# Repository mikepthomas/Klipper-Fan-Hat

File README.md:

# Klipper Fan Hat

[Interactive bom](https://mikethomas.info/Klipper-Fan-Hat)

### A Hat to use with the [Raspberry Pi as a Secondary MCU in Klipper](https://www.klipper3d.org/RPi_microcontroller.html):
- SKR Pico compatible input for powering the Pi and Serial communication
- 5 Mosfet outputs (with 2 pin JST-XH connectors standard on most fans used on 3D printers)
- Voltage selector jumpers to power each fan from either 5V or VCC supplied by screw terminal
- I2C and 1-Wire and SPI headers for connecting accesories to the Raspberry Pi
- 2 headers connected to General Purpose GPIO pins for accesories such as Filament Run Out Sensors

### Documentation

[Documentation and Setup information here](Documentation/README.md)

 Parts that I sourced for assembly:
- 1206 Capacitor Set [Ali Express](https://www.aliexpress.com/item/1005002907508304.html)
- 1206 LEDs [Ali Express](https://www.aliexpress.com/item/1005003836509392.html)
- 1206 Resistor Set [Ali Express](https://www.aliexpress.com/item/33029877427.html)
- 2510 Axial Fan [Ali Express](https://www.aliexpress.com/item/32807610078.html)
- Blade Fuse Holder [Ali Express](https://www.aliexpress.com/item/1005003194700697.html)
- DIP-8 24C32 EEPROM [Ali Express](https://www.aliexpress.com/item/33036366759.html)
- DIP-8 Socket [Ali Express](https://www.aliexpress.com/item/1005001650813894.html)
- IRLML6344TRPBF Mosfets [Ali Express](https://www.aliexpress.com/item/1005004711783484.html)
- JST-XH Connector Set [Ali Express](https://www.aliexpress.com/item/33000442968.html)
- Jumper Caps [Ali Express](https://www.aliexpress.com/item/1005004482029258.html)
- KF301 Screw Terminal [Ali Express](https://www.aliexpress.com/item/1005003311688833.html)
- M2.5x14 BHCS [Ali Express](https://www.aliexpress.com/item/1005004123548619.html)
- Pin Header Set [Amazon](https://www.amazon.co.uk/gp/product/B07CWSXY7P)
- Raspberry Pi Headers and Spacers [Amazon](https://www.amazon.co.uk/gp/product/B07PHBTTGV)

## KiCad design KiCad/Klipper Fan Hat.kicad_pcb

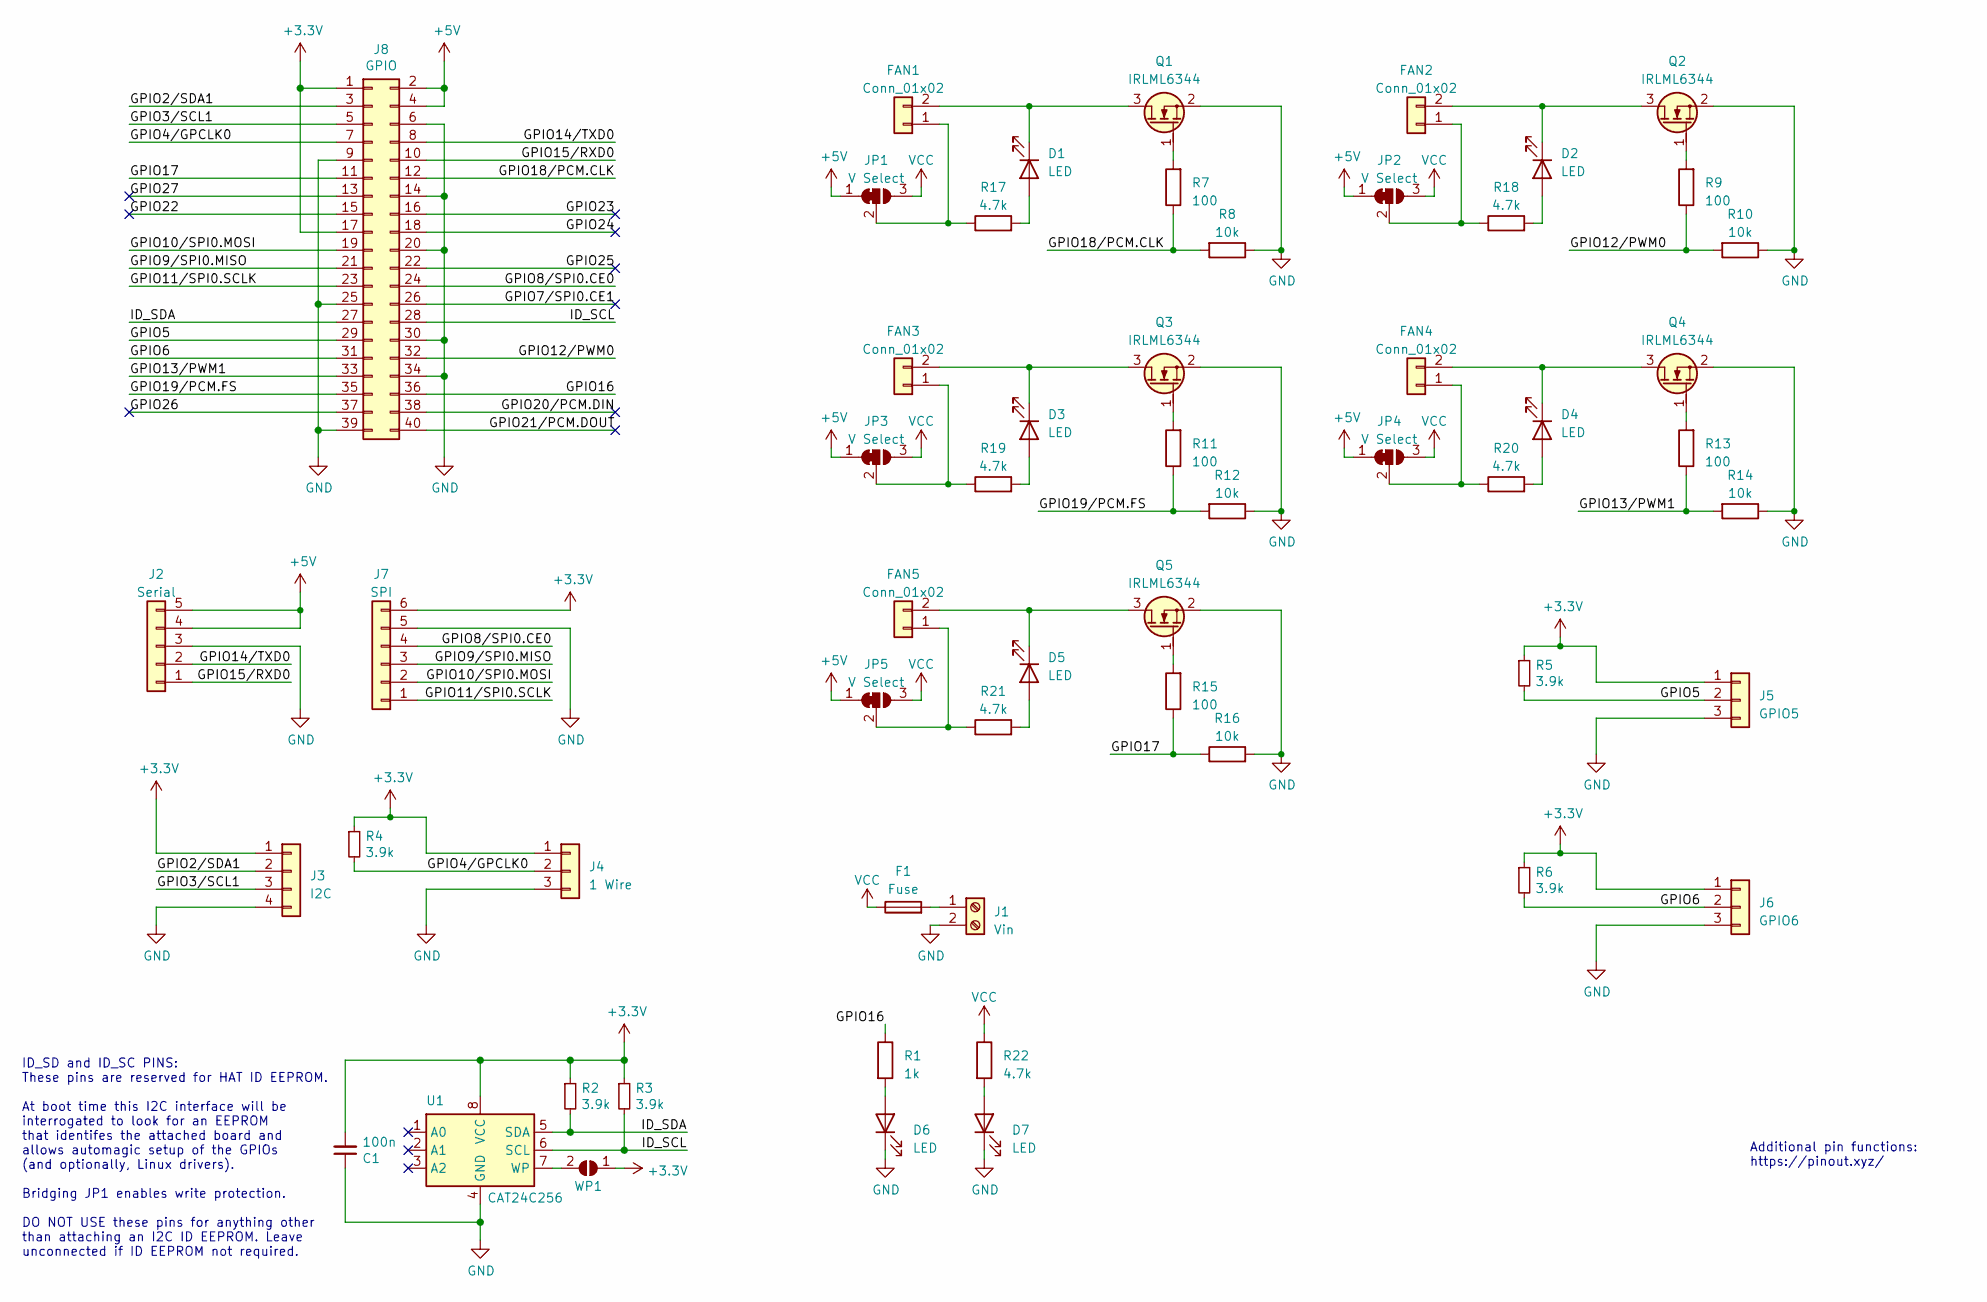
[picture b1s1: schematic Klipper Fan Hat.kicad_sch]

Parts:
C1: 100n; C_1206_3216Metric
D1, D2, D3, D4, D5, D6, D7: LED; LED_1206_3216Metric_ReverseMount_Hole1.8x2.4mm
F1: Fuse; Fuseholder_Blade_Mini_Keystone_3568
FAN1, FAN2, FAN3, FAN4, FAN5: Conn_01x02; JST_XH_B2B-XH-A_1x02_P2.50mm_Vertical
J1: Vin; TerminalBlock_bornier-2_P5.08mm
J2: Serial; JST_XH_B5B-XH-A_1x05_P2.50mm_Vertical
J3: I2C; JST_XH_B4B-XH-A_1x04_P2.50mm_Vertical
J4: 1 Wire; JST_XH_B3B-XH-A_1x03_P2.50mm_Vertical
J5: GPIO5; JST_XH_B3B-XH-A_1x03_P2.50mm_Vertical
J6: GPIO6; JST_XH_B3B-XH-A_1x03_P2.50mm_Vertical
J7: SPI; PinHeader_1x06_P2.54mm_Vertical
J8: GPIO; PinSocket_2x20_P2.54mm_Vertical
JP1, JP2, JP3, JP4, JP5: V Select; PinHeader_1x03_P2.54mm_Vertical
Q1, Q2, Q3, Q4, Q5: IRLML6344; TSOT-23
R1: 1k; R_1206_3216Metric
R2, R3, R4, R5, R6: 3.9k; R_1206_3216Metric
R7, R9, R11, R13, R15: 100; R_1206_3216Metric
R8, R10, R12, R14, R16: 10k; R_1206_3216Metric
R17, R18, R19, R20, R21, R22: 4.7k; R_1206_3216Metric
U1: CAT24C256; DIP-8_W7.62mm
WP1: ID_WP; PinHeader_1x02_P2.54mm_Vertical

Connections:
+3V3: C1.2, J3.1, J4.1, J5.1, J6.1, J7.6, J8.1, J8.17, R2.1, R3.1, R4.1, R5.1, R6.1, U1.8 (VCC), WP1.1 (A)
+5V: J2.4, J2.5, J8.2, J8.4, JP1.1 (A), JP2.1 (A), JP3.1 (A), JP4.1 (A), JP5.1 (A)
/GPIO2/SDA1: J3.2, J8.3
/GPIO3/SCL1: J3.3, J8.5
/GPIO4/GPCLK0: J4.2, J8.7, R4.2
/GPIO5: J5.2, J8.29, R5.2
/GPIO6: J6.2, J8.31, R6.2
/GPIO7/SPI0.CE1: J8.26
/GPIO8/SPI0.CE0: J7.4, J8.24
/GPIO9/SPI0.MISO: J7.3, J8.21
/GPIO10/SPI0.MOSI: J7.2, J8.19
/GPIO11/SPI0.SCLK: J7.1, J8.23
/GPIO12/PWM0: J8.32, R9.1, R10.2
/GPIO13/PWM1: J8.33, R13.1, R14.2
/GPIO14/TXD0: J2.2, J8.8
/GPIO15/RXD0: J2.1, J8.10
/GPIO16: J8.36, R1.1
/GPIO17: J8.11, R15.1, R16.1
/GPIO18/PCM.CLK: J8.12, R7.1, R8.2
/GPIO19/PCM.FS: J8.35, R11.1, R12.2
/GPIO20/PCM.DIN: J8.38
/GPIO21/PCM.DOUT: J8.40
/GPIO22: J8.15
/GPIO23: J8.16
/GPIO24: J8.18
/GPIO25: J8.22
/GPIO26: J8.37
/GPIO27: J8.13
/ID_SCL: J8.28, R3.2, U1.6 (SCL)
/ID_SDA: J8.27, R2.2, U1.5 (SDA)
GND: C1.1, D6.1 (K), D7.1 (K), J1.2, J2.3, J3.4, J4.3, J5.3, J6.3, J7.5, J8.6, J8.9, J8.14, J8.20, J8.25, J8.30, J8.34, J8.39, Q1.2 (S), Q2.2 (S), Q3.2 (S), Q4.2 (S), Q5.2 (S), R8.1, R10.1, R12.1, R14.1, R16.2, U1.4 (GND)
unnamed: D1.2 (A), R17.2
unnamed: D1.1 (K), FAN1.2, Q1.3 (D)
unnamed: D2.2 (A), R18.2
unnamed: D2.1 (K), FAN2.2, Q2.3 (D)
unnamed: D3.2 (A), R19.2
unnamed: D3.1 (K), FAN3.2, Q3.3 (D)
unnamed: D4.2 (A), R20.2
unnamed: D4.1 (K), FAN4.2, Q4.3 (D)
unnamed: D5.2 (A), R21.2
unnamed: D5.1 (K), FAN5.2, Q5.3 (D)
unnamed: D6.2 (A), R1.2
unnamed: D7.2 (A), R22.2
unnamed: FAN1.1, JP1.2 (C), R17.1
unnamed: FAN2.1, JP2.2 (C), R18.1
unnamed: FAN3.1, JP3.2 (C), R19.1
unnamed: FAN4.1, JP4.2 (C), R20.1
unnamed: FAN5.1, JP5.2 (C), R21.1
unnamed: F1.2, J1.1
unnamed: Q1.1 (G), R7.2
unnamed: Q2.1 (G), R9.2
unnamed: Q3.1 (G), R11.2
unnamed: Q4.1 (G), R13.2
unnamed: Q5.1 (G), R15.2
unnamed: U1.7 (WP), WP1.2 (B)
VCC: F1.1, JP1.3 (B), JP2.3 (B), JP3.3 (B), JP4.3 (B), JP5.3 (B), R22.1

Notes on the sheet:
Additional pin functions: https://pinout.xyz/
ID_SD and ID_SC PINS: These pins are reserved for HAT ID EEPROM. At boot time this I2C interface will be interrogated to look for an EEPROM that identifes the attached board and allows automagic setup of the GPIOs (and optionally, Linux drivers). Bridging JP1 enables write protection. DO NOT USE th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

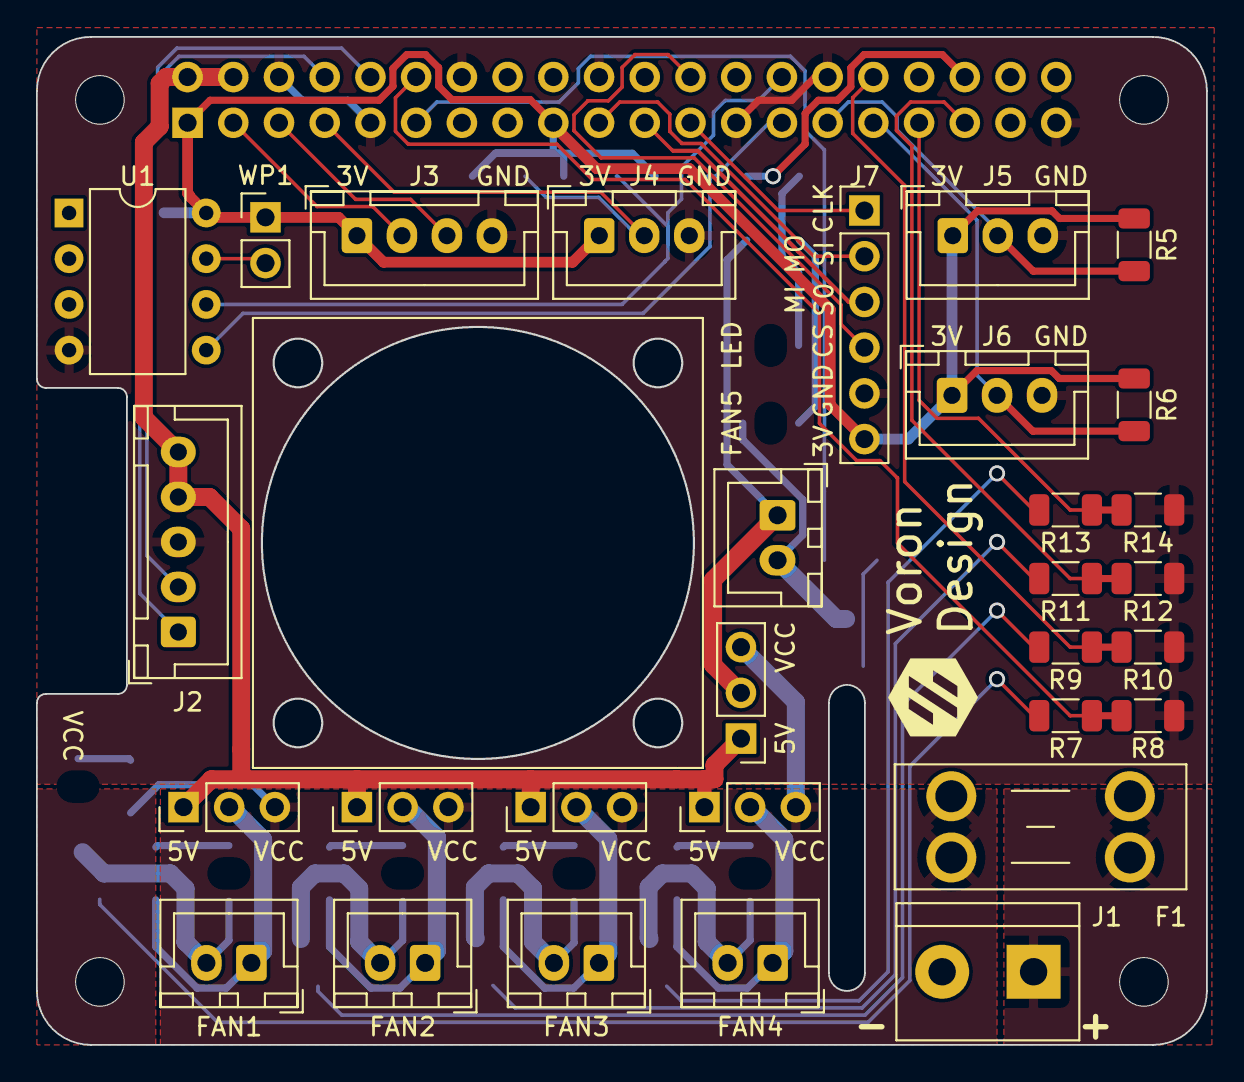
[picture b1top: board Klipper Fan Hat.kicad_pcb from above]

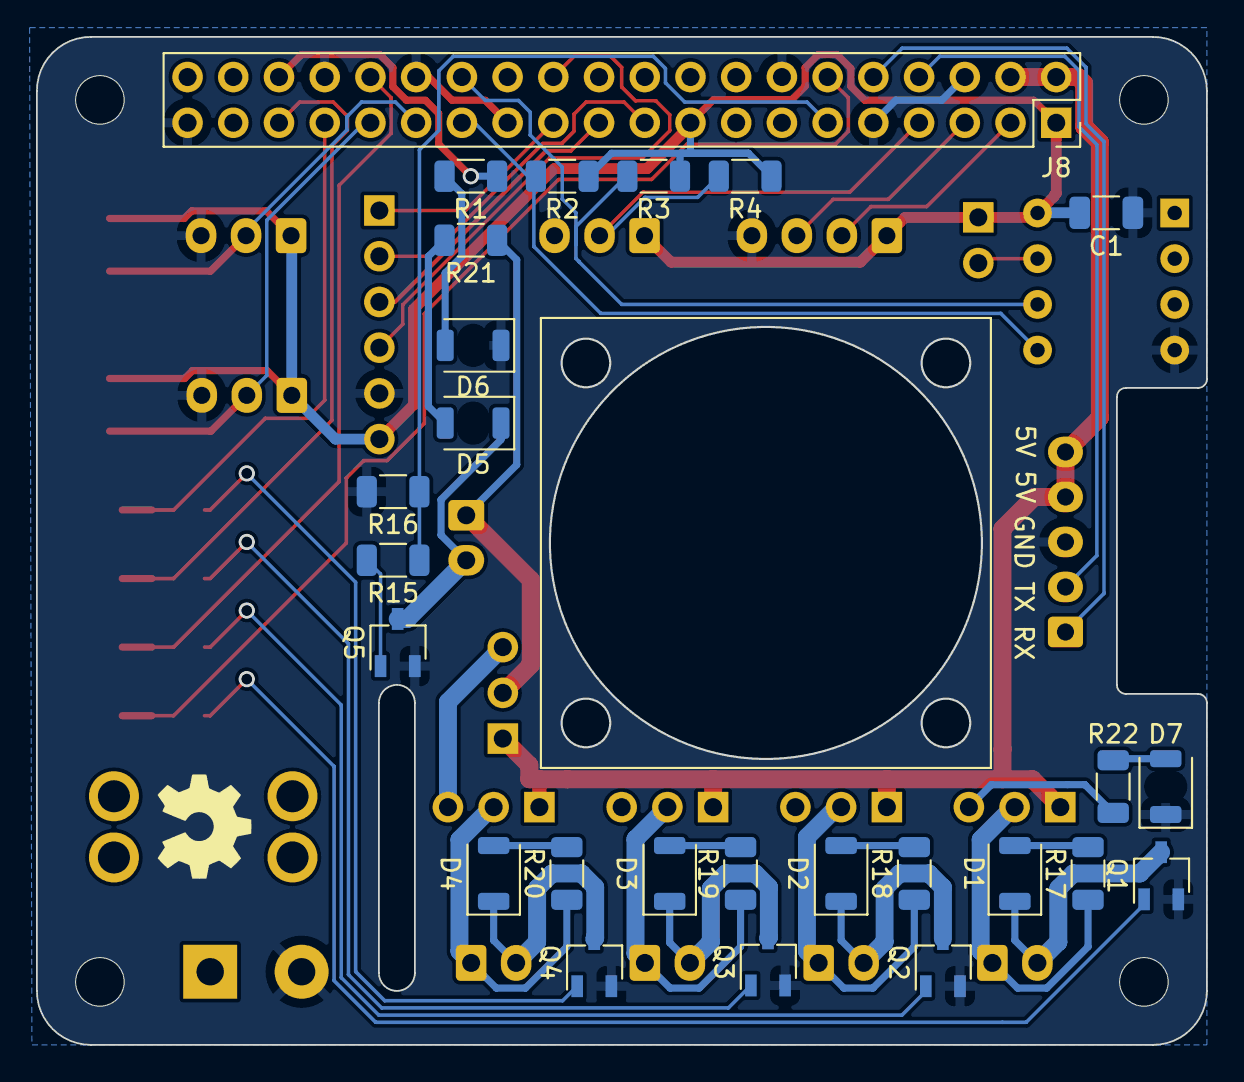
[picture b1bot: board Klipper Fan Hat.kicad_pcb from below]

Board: 2 copper layers, 65.0 x 56.0 mm, 60 parts (26 on the bottom side), 47 nets.

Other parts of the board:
MH1, MH2, MH3, MH4: MountingHole_2.7mm_M2.5

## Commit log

2023-03-21 Add Version 1
2023-03-28 Add EEPROM settings file
2023-03-29 Update product id and version number, and add device tree overlay source file to automatically enable SPI and I2C at the correct baud rate
2023-03-30 Rename to Klipper Fan Hat
2023-04-21 Update Klipper Fan Hat to V2
2023-04-21 Create LICENSE
2023-04-26 Update Klipper Fan Hat software to V2
2023-04-26 GPIO 16 is used for status LED
2023-04-26 Add gh-pages
2023-04-26 Add version number
2023-04-27 Update Klipper Config
2023-04-28 Add Basic ReadMe
2023-04-28 Add Klipper Setup Documentation and Component Images
2023-04-28 Describe the connectors
2023-04-28 fix broken link
2023-04-29 Add EEPROM flashing ReadMe file
2023-04-29 Add link to EEPROM flashing guide

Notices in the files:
KiCad/Klipper Fan Hat.kicad_pcb:
GNU General Public License v3.0
